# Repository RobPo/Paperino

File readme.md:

Paperino PL_microEPD Arduino Library
===============================================================

Welcome to the Paperino docs! This is a Hardware Library for the 1.1” E-Paper display (EPD) from Plastic Logic for Adafruits GFX library. 

[*Paperino E-Paper Shield for Particle, Breakout Board and Driver Module*](https://www.crowdsupply.com/robert-poser/paperino)

### So, what is Paperino?

Paperino is an easy to use micro EPD breakout-board for the Photon or other Arduino-compatible microcontrollers. The eInk-based ePaper display mimics the appearance of natural paper and is capable of holding text and images indefinitely, even without electricity. This makes Paperino perfect for your next battery-driven, connected project where the display content changes rarely.

Paperino also integrates an easy to use accelerometer. It extends the EPD by tap-sensing functions and offers portrait/landscape detection. Furthermore you can wake-up your MCU after movement-based events from deep-sleeping, saving battery live during waiting phases.

Featured In
-------------------

Documentation
--------------
This is the place to get started with your new hardware! We have divided the documentation into the following sections:

* **[Hookup Guide](https://robpo.github.io/Paperino/)** - Step-by-step instructions to get your Paperino setup and run within minutes.
* **[Examples](https://robpo.github.io/Paperino/exampleHelloWorld/)** - Ready to use examples for your own inspiration.
* **[Reference](https://github.com/RobPo/Paperino/tree/gh-pages/datasheets)** - Datasheets & Application Notes.
* **[Hardware](https://github.com/RobPo/Paperino/tree/gh-pages/hardware)** - Schematics & PCB layouts.

How To Use
-------------------

### Installation

This library is part of the Particle and Arduino **Library Manager**. Please search for `PL_microEPD` within the Manager and download the library, that’s it! Included are six example sketches, they are useful to learn the basics about this ePaper screen.

### Hardware hookup

To start communicating with the ePaper driver IC, you’ll need to supply 3.3V and four more wires for SPI communication (@3.3V voltage level). Please have a look at the [hook-up guide](https://robpo.github.io/Paperino/) for more detailed information. 

### Example: Hello World!

This is the [first](https://robpo.github.io/Paperino/exampleHelloWorld/), and shortest possible demo and shows how to address the ePaper (don’t forget to update the GPIO name if needed in line 3):

```cpp
#include "Adafruit_GFX.h"
#include "PL_microEPD.h"

#define EPD_CS      A2
PL_microEPD display(EPD_CS);  

void setup() {  
    SPI.begin();                    
    SPI.beginTransaction(SPISettings(4000000, MSBFIRST, SPI_MODE0));
  
    display.begin();                
    display.print("Hello World!");
    display.update();               
}

void loop() {              
}
```

You should now be able to see the ePaper screen updating. Congratulation! If you feel more like a pro’ this is now the time to [add the wiring](https://robpo.github.io/Paperino/) of two more GPIO lines (called ‘busy’ & ‘reset’). They are needed to run the image updates a bit faster and/or to reset the IC after having it set to deep sleep.

### More…

Once this example is successfully running, please have a look at the following sketches: [GFX demo](https://robpo.github.io/Paperino/exampleGFXdemo/) shows how to draw all the letters, rectangles and dots. The [Graylevel](https://robpo.github.io/Paperino/example4GLs/) sketch explains how to use the four different graylevels in your next project. [Update modes](https://robpo.github.io/Paperino/exampleUpdateMode/) describes three different ways of updating an ePaper screen.

Distributors
-------------------
Paperino ePaper displays are available at [Crowd Supply](https://www.crowdsupply.com/robert-poser/paperino), [Watterott electronic](http://www.watterott.com/de/Paperino-A-micro-ePaper-with-accelerometer), [Mouser](https://www2.mouser.com/Search/Refine.aspx?Keyword=paperino) and [DigiKey](https://www.digikey.com/products/en?keywords=paperino).

Projects
-------------------
These demo projects are for your inspiration! What will you implement with Paperino? Tell us, we’ll love to add your project here!

Changelog
-------------------
- [v1.1.01 (03/2018)](https://github.com/RobPo/Paperino/archive/v1.1.01.zip) - Add support for more EPDs: 1.4", 2.1" & 3.1" (auto-detection) and for deepSleep() of driver IC
- [v1.0.20 (10/2017)](https://github.com/RobPo/Paperino/archive/v1.0.20.zip) - Add support for (optional) simplified wiring for MCUs with limited GPIOs
- [v1.0.10 (08/2017)](https://github.com/RobPo/Paperino/archive/v1.0.10.zip) -  Particle & Arduino Library Manager supported; tap sensitivity increased; ‘verified’ by Particle
- [v1.0.00 (07/2017)](https://github.com/RobPo/Paperino/archive/v1.0.06.zip) - Initial release

License Information
-------------------

This library is _**open source**_!

Created by Robert Poser, Mar 4th 2018, Dresden/Germany. Released under BSD license (3-clause BSD license), check license.md for more information.

We invested time and resources providing this open source code, please support Paperino and 
open source hardware @Adafruit and by purchasing this product @Crowdsupply @Watterott @Plasticlogic.

If you like this project please [follow us on Twitter](https://twitter.com/paperino_io).
Having problems or have awesome suggestions? Contact us: paperino.display@gmail.com.

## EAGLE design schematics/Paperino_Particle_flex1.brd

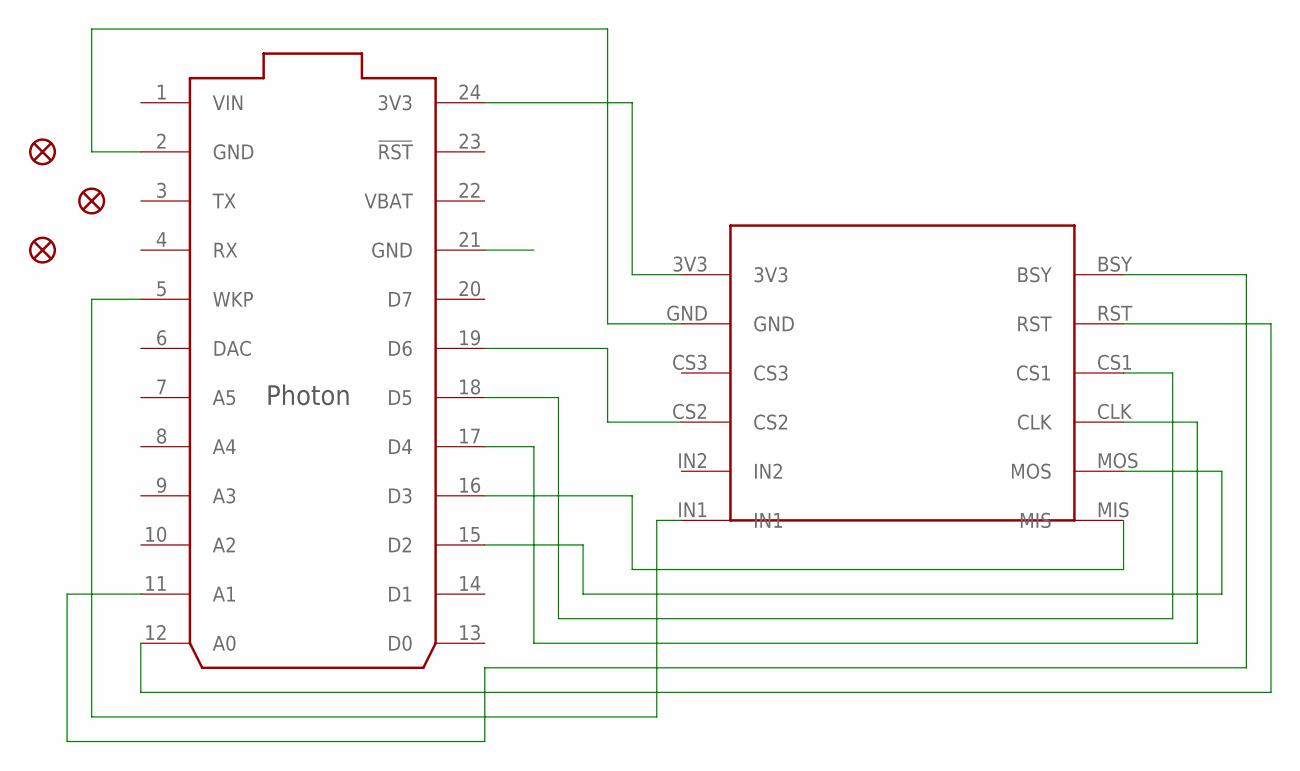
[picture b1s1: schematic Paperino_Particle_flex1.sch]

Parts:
FD1, FD2, FD3: FIDUCIAL1X2; FIDUCIAL-1X2
U$1: PHOTON_WITH_HEADERS; PHOTON
U$2: S1-MODULE

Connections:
GND: U$1.2 (GND), U$1.21 (GND), U$2.GND
unnamed: U$1.12 (A0), U$2.RST
unnamed: U$1.24 (3V3), U$2.3V3
unnamed: U$1.19 (D6), U$2.CS2
unnamed: U$1.18 (D5), U$2.CS1
unnamed: U$1.17 (D4), U$2.CLK
unnamed: U$1.16 (D3), U$2.MIS
unnamed: U$1.15 (D2), U$2.MOS
unnamed: U$1.11 (A1), U$2.BSY
unnamed: U$1.5 (WKP), U$2.IN1
VBAT: U$1.22 (VBAT)
VIN: U$1.1 (VIN)

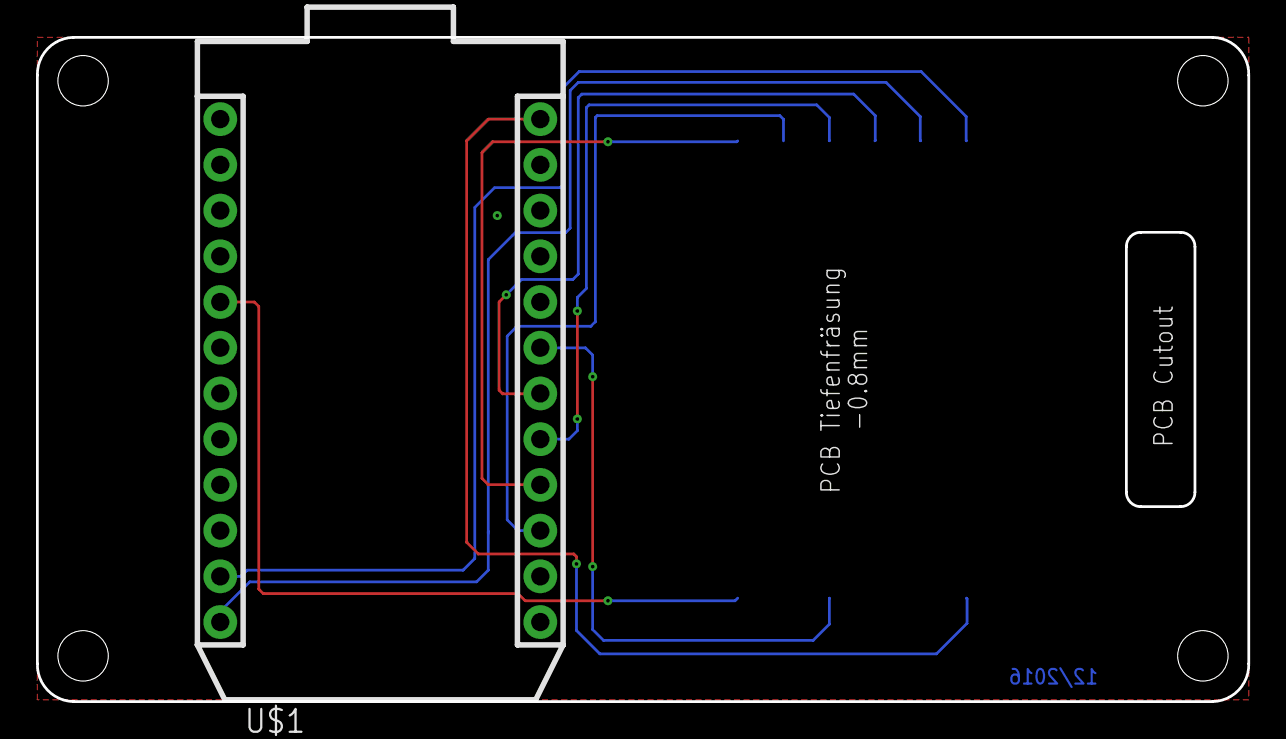
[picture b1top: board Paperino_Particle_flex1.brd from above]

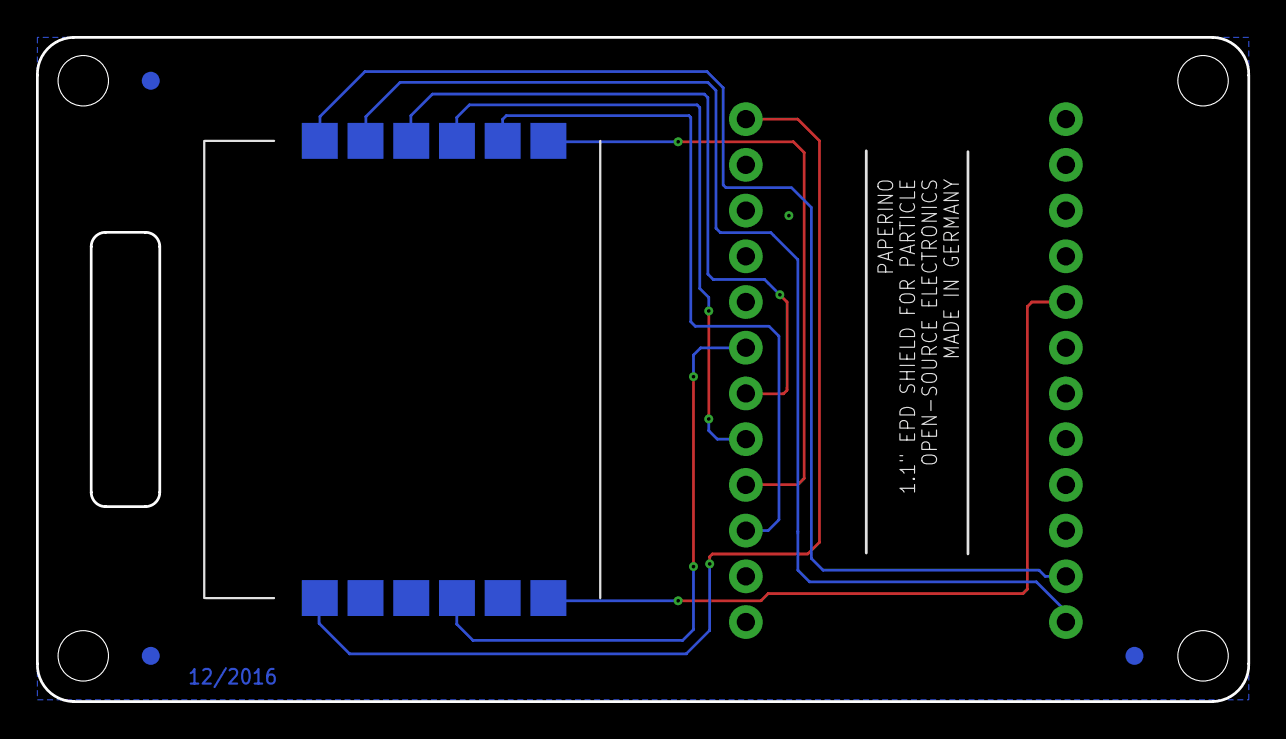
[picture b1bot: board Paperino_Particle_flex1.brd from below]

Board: 2 copper layers, 67.3 x 36.9 mm, 5 parts (4 on the bottom side), 10 nets.

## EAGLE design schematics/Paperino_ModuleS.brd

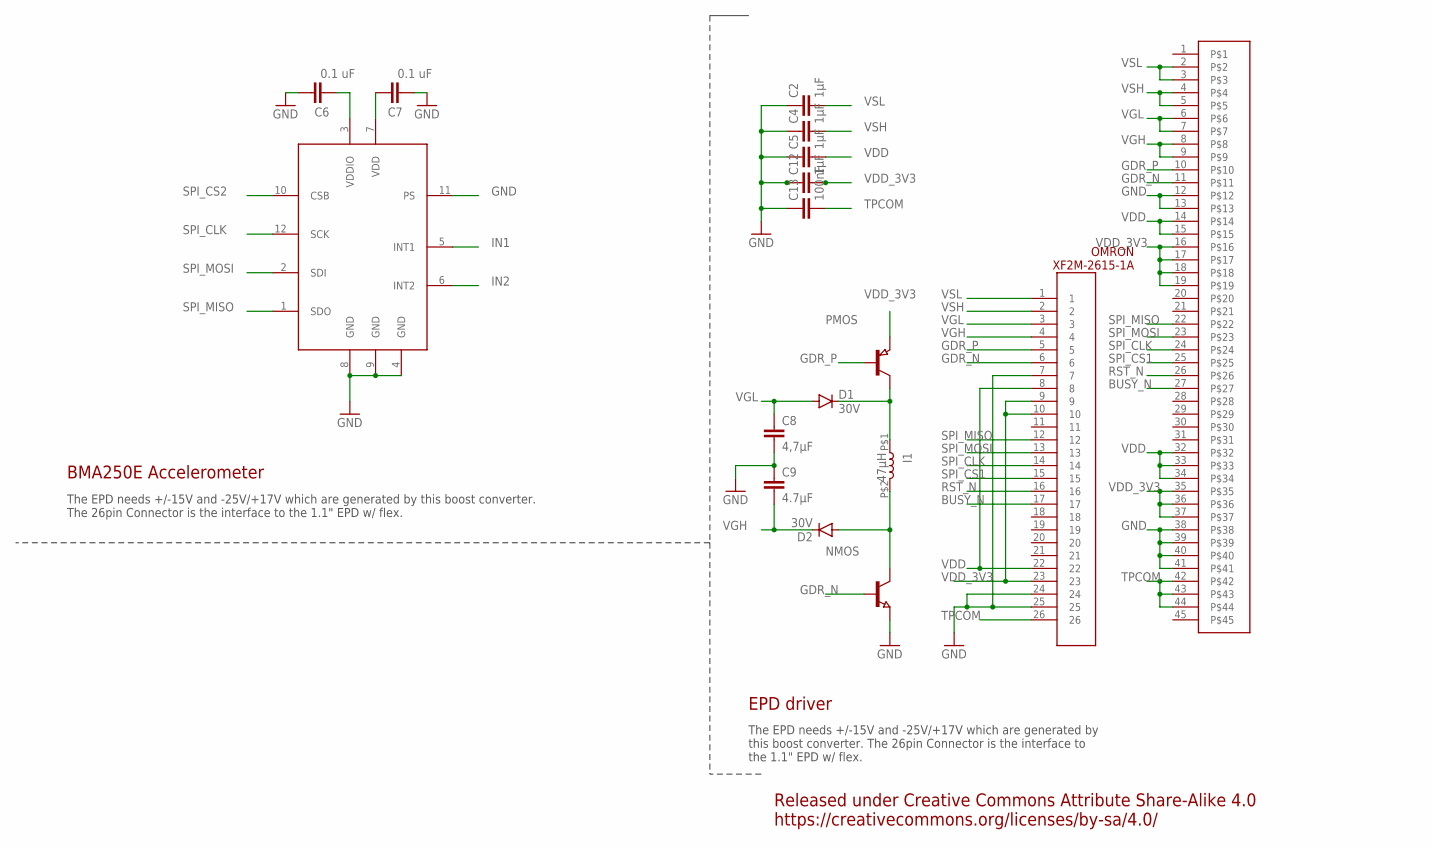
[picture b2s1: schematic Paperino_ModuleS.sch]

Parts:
BMA250: BMA250; 12LGA_VGG3-D
C2, C4, C5, C12: 1µF; 0603-CAP
C6, C7: 0.1 uF; C0402
C8: 4,7µF; 0805
C9: 4.7µF; 0805
C13: 100nF; 0603-CAP
D1, D2: 30V; SOD-323
I1: 47µH; I_4017_PAC
NMOS: NPN-TRANSISTOR_SOT23; SOT23
PMOS: PNP-TRANSISTOR_SOT23; SOT23
U$3: OMRON-X2FM-DEV2; OMRON-X2FM-26PIN-PAC
U$4: OMRON-XF2B

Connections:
BUSY_N: U$3.17, U$4.27
GDR_N: NMOS.1 (B), U$3.6, U$4.11
GDR_P: PMOS.1 (B), U$3.5, U$4.10
GND: BMA250.4 (GND), BMA250.8 (GND), BMA250.9 (GND), BMA250.11 (PS), C2.1, C4.1, C5.1, C6.1, C7.2, C8.2, C9.1, C12.1, C13.1, NMOS.2 (E), U$3.7, U$3.24, U$3.25, U$4.12, U$4.13, U$4.38, U$4.39, U$4.40, U$4.41
IN1: BMA250.5 (INT1)
IN2: BMA250.6 (INT2)
unnamed: D2.A, I1.P$2 (2), NMOS.3 (C)
unnamed: D1.C, I1.P$1 (1), PMOS.3 (C)
RST_N: U$3.16, U$4.26
SPI_CLK: BMA250.12 (SCK), U$3.14, U$4.24
SPI_CS1: U$3.15, U$4.25
SPI_CS2: BMA250.10 (CSB)
SPI_MISO: BMA250.1 (SDO), U$3.12, U$4.22
SPI_MOSI: BMA250.2 (SDI), U$3.13, U$4.23
TPCOM: C13.2, U$3.26, U$4.42, U$4.43, U$4.44
VDD: C5.2, U$3.8, U$3.22, U$4.14, U$4.15, U$4.32, U$4.33, U$4.34
VDD_3V3: BMA250.3 (VDDIO), BMA250.7 (VDD), C6.2, C7.1, C12.2, PMOS.2 (E), U$3.9, U$3.10, U$3.23, U$4.16, U$4.17, U$4.18, U$4.19, U$4.35, U$4.36, U$4.37
VGH: C9.2, D2.C, U$3.4, U$4.8, U$4.9
VGL: C8.1, D1.A, U$3.3, U$4.6, U$4.7
VSH: C4.2, U$3.2, U$4.4, U$4.5
VSL: C2.2, U$3.1, U$4.2, U$4.3

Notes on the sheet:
The EPD needs +/-15V and -25V/+17V which are generated by this boost converter. The 26pin Connector is the interface to the 1.1" EPD w/ flex.
The EPD needs +/-15V and -25V/+17V which are generated by this boost converter. The 26pin Connector is the interface to the 1.1" EPD w/ flex.
EPD driver
BMA250E Accelerometer
Released under Creative Commons Attribute Share-Alike 4.0 https://creativecommons.org/licenses/by-sa/4.0/

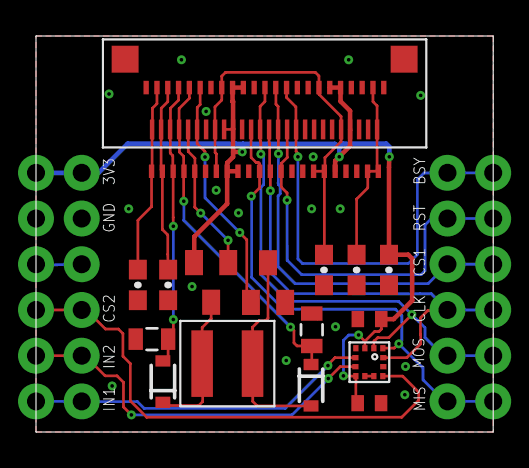
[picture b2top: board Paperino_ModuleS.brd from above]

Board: 2 copper layers, 25.4 x 22.0 mm, 17 parts (0 on the bottom side), 18 nets.

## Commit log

2017-01-23 :octocat: Added .gitattributes & .gitignore files
2017-01-23 Readme added
2017-01-23 Schematics added
2017-01-23 Link updated
2017-01-24 HelloWorld demo added
2017-01-24 HelloWorld demo2 added
2017-01-24 GFXdemo added
2017-01-24 Demo added
2017-01-24 Demo added!
2017-01-25 UpdateMode Demo added
2017-01-26 Examples added
2017-01-26 modified description
2017-01-26 descry added
2017-01-26 Demos updated
2017-02-01 Updated!
    PLD_tinyEPD changed to PL_microEPD
2017-02-01 name conversion
    PLD_tinyEPD changed to PL_microEPD
2017-02-15 Update 01_HelloWorld.ino
    fixed print staement
2017-02-15 Update 01_HelloWorld.ino
    added setCursor to ensure correct text display
2017-02-17 Create check
2017-02-17 New Pic set added!
2017-02-18 The holy tripel!
2017-03-08 Addresses: Issue #2
2017-05-05 update hardware files to KiCad
2017-07-23 Lib 1.0.0 release
2017-07-23 Readme
    description added
2017-07-23 rm
    updated
2017-07-23 desc
    updated
2017-07-23 read_me
    updated
2017-07-23 documentation updated!
2017-07-24 Description updated
2017-07-24 paragraph, category added
2017-07-24 Hookup guide started
2017-07-26 Link to Project TrafficIndicator added
2017-07-26 img size scaled
2017-07-27 Project link added
2017-07-27 layout changed
2017-07-27 layout adjusted
2017-07-27 Tap sensitivity increased
2017-07-27 CS_Accel adjusted to match with shield pinout
2017-07-28 as featured in added
2017-07-28 featured in updated
2017-07-28 Access sensitivity increased & repo added
2017-07-30 email address corrected
2017-07-31 first fritzing breadboards added
2017-07-31 link added
2017-07-31 hookup link adjusted
2017-07-31 link & email corrected
2017-07-31 Home deleted
2017-07-31 link adjusted
2017-07-31 image upload
2017-08-02 wemods pinout added
2017-08-03 img update
2017-08-03 image added
2017-08-03 more frizzing added (nodemcu)
2017-08-03 name changed
2017-08-04 Frizzing Rasp img added
2017-08-05 image slider test
2017-08-05 frizzing slider
2017-08-05 header turned-off
2017-08-05 links adjusted
2017-08-06 hookup updated
2017-08-07 tap demo added
2017-08-08 twitter link added
2017-08-08 twitter link
2017-08-08 tw updated
2017-08-08 twitter link added.
2017-08-08 pentacast added
2017-08-08 Revert "Delete DemoTap.GIF"
    This reverts commit bf089c1f8bcb4f5a9311977469919005b14d332a.
2017-08-08 review name
2017-08-08 small letters
2017-08-09 Arduino Lib added
2017-08-09 descr. added
2017-08-09 link corrected
2017-08-10 Library Manager supported
2017-08-10 back to repo added
2017-08-10 back added
2017-08-10 example1 corrected
2017-08-23 #define ACC_CS adjusted to D6
2017-08-24 installation section added
2017-08-26 Project rainforecast added
2017-08-26 readme.md image files moved out of repo to issue
2017-08-26 images moved to issue to reduce repo size
2017-08-26 Fresh start for documentation in separate branch
2017-08-26 Create LICENSE
2017-08-26 Library manager descr added
2017-08-26 reduce repo size
2017-08-27 index.html moved
2017-08-27 Set theme jekyll-theme-cayman
2017-08-27 website moved to gh-pages
2017-08-27 docs folder removed from master
2017-08-27 data sheets moved to gh-pages branch
2017-08-27 datasheets moves to gh-pages branch
2017-08-27 hardware files moved th gh-pages branch
2017-08-27 hardware files moved to gh-pages branch & link updated
2017-08-27 library manager added
2017-08-27 typo
2017-08-27 new release
2017-09-03 created
2017-09-28 Watterott added
2017-09-28 descrption updated
2017-10-03 Example code added
2017-10-03 Example added
2017-10-03 example added, wiring short descr. still open
2017-10-04 reverting
2017-10-05 description added
2017-10-05 description updated & extended
2017-10-05 Busy&reset pin made optional; replaced by software reset&delay
2017-10-05 Changelog added
2017-10-05 new release w/ optional rst&bsy pin
2017-10-07 link to new release added
2017-11-06 tap tap machine project added
2017-11-06 project tap tap machine added
2017-11-06 project tap tap machine
2018-01-28 fixed file permissions (0755 -> 0644)
2018-01-28 fixed warning: extra tokens at end of #ifdef directive
2018-01-28 fixed warning: comparison between signed and unsigned integer expressions
2018-01-29 fixed warning: comparison is always true due to limited range of data type
2018-01-30 Removed old and duplicate version of header.
2018-02-08 Support & auto detection for larger displays sizes added. deep-sleep added
2018-02-08 support for larger EPDs added. deep sleep added
2018-02-09 Std. wiring to demos added
2018-02-09 Std wiring to demos added
2018-03-04 More Distributors added
2018-03-04 Changeling updated
2018-03-04 Changelog updated
2018-03-04 license date updated
2018-03-04 Timing adjustments to increase stability
2018-06-03 Changed 'BSD 3-Clause' license to have a capital C
2018-06-14 Use semver compliant version in library.properties
    Non-semver compliant version value causes the Arduino IDE to display warnings:
    Invalid version found: 1.1.02
    This can be especially confusing for users since the Arduino IDE doesn't say which library is the source of the problem.
    References:
    - https://github.com/arduino/Arduino/wiki/Arduino-IDE-1.5:-Library-specification#libraryproperties-file-format
    - https://semver.org/
2020-01-06 Specify library dependencies in library.properties
    Specifying the library dependencies in the depends field of library.properties causes the Arduino Library Manager (Arduino IDE 1.8.10 and newer) to offer to install any missing dependencies during in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
2021-05-13 Use specification compliant sketch names
    From the Arduino Sketch Specification:
    https://arduino.github.io/arduino-cli/dev/sketch-specification/#sketch-folders-and-files
    > The sketch root folder name and code file names must start with a basic letter (A-Z or a-z) or number (0-9), followed
    > by basic letters, numbers, underscores (_), dots (.) and dashes (-).

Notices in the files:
parts and their libraries:
SparkFun-Capacitors: Licensing: Creative Commons ShareAlike 4.0 International - https://creativecommons.org/licenses/by-sa/4.0
